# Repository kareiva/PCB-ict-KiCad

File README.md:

# PCB-ict-KiCad
The ICT tracker KiCad PCB imported from @micked99's Eagle version

Based on original ict_v361 - using the TQFP version of the 328p - Verified working

Software for this board: https://github.com/kareiva/ICT-v5-ATGM336

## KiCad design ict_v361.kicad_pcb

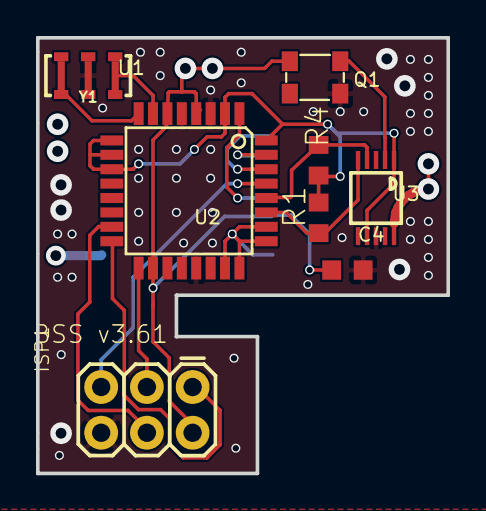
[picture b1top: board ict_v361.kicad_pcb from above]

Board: 2 copper layers, 22.8 x 24.2 mm, 9 parts (1 on the bottom side), 16 nets.

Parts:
C4: 1uF 0603; C0603K
ISP1: AVR_SPI_PRG_6PTH; 2X3
Q1: KXO-TCXO-CMOS-84; 3.2X2.5_KXO-84-TCXO
R1, R4: R-EU_R0603; R0603
U2: ATMEGA328P; TQFP32-08
U3: Si5351A-B-GT; MSOP10
U$2: UBLOX_MAX
Y1: RESONATORSMD-4.5X2.0; RESONATOR-SMD-4.5X2.0

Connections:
/ENABLE: R1.2, R4.2, U2.2, U2.9, U2.10, U2.11, U2.32, U3.1, U3.7
/GPS-OFF: U2.1, U$2.5_EXTINT0
/GPS_ON_OFF: U2.23, U2.24, U2.25, U2.26, U$2.8_VCC
/MISO: ISP1.1, U2.16
/MOSI: ISP1.4, U2.15
/RESET: ISP1.5, U2.29
/SCK: ISP1.3, U2.17
/SCL: R4.1, U2.28, U3.4
/SDA: R1.1, U2.27, U3.5
/SERIAL_IN: U2.30, U$2.2_TXD1
/SERIAL_OUT: U2.31, U$2.3_RXD1
/VIN: C4.1, ISP1.2, Q1.4, U2.4, U2.6, U2.18, U$2.6_V_BCKP
GND: C4.2, ISP1.6, Q1.2, U2.3, U2.5, U2.21, U3.8, U$2.1_GND, U$2.10_GND, U$2.12_GND, Y1.2
unnamed: Q1.3, U3.2
unnamed: U2.7, Y1.1
unnamed: U2.8, Y1.3

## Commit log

2022-05-09 Import from micked99 Eagle version to KiCad6
